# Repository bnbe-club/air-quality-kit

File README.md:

# air-quality-kit
The design files for the air quality kit based on the Piksey Pico and SGP30 sensor.

YouTube Video: https://www.youtube.com/watch?v=lpBCYy5J5to
Website Post: https://www.bitsnblobs.com/air-quality-sensor-kit

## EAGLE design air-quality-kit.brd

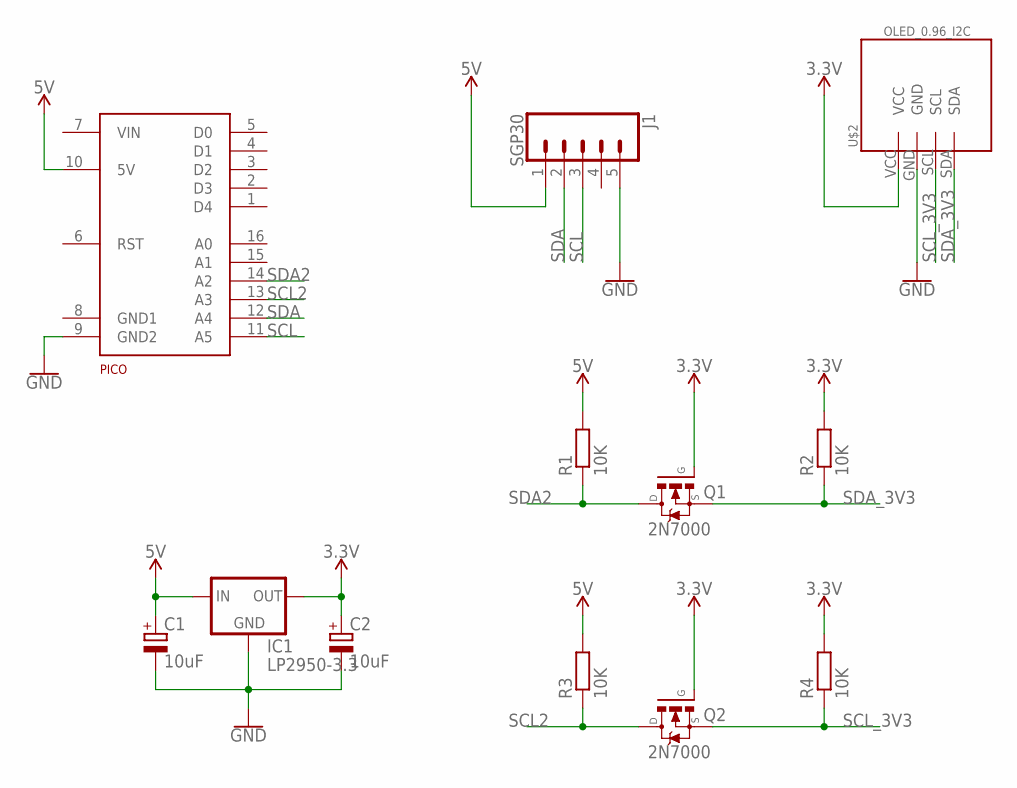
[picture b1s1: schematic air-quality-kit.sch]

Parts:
C1, C2: 10uF; E2,5-5
IC1: LP2950-3.3; TO92
J1: SGP30; 1X05
PICO: PICO
Q1, Q2: 2N7000; TO-92
R1, R2, R3, R4: 10K; 0207/10
U$2: OLED_0.96_I2C

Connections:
3.3V: C2.+, IC1.1 (OUT), Q1.2 (G), Q2.2 (G), R2.2, R4.2, U$2.VCC
5V: C1.+, IC1.3 (IN), J1.1, PICO.10 (5V), R1.2, R3.2
GND: C1.-, C2.-, IC1.2 (GND), J1.5, PICO.9 (GND2), U$2.GND
SCL: J1.3, PICO.11 (A5)
SCL2: PICO.13 (A3), Q2.3 (D), R3.1
SCL_3V3: Q2.1 (S), R4.1, U$2.SCL
SDA: J1.2, PICO.12 (A4)
SDA2: PICO.14 (A2), Q1.3 (D), R1.1
SDA_3V3: Q1.1 (S), R2.1, U$2.SDA

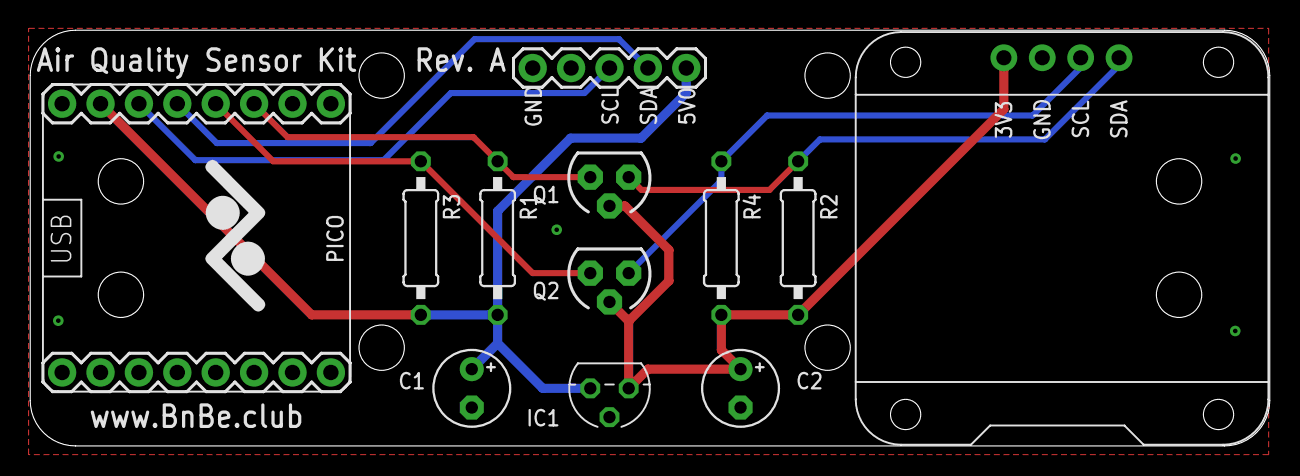
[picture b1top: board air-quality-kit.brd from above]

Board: 2 copper layers, 82.0 x 27.5 mm, 12 parts (0 on the bottom side), 9 nets.

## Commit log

2019-12-14 Added files for rev. A
2019-12-14 Added YouTube and website links

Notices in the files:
parts and their libraries:
SparkFun-Connectors: Licensing: Creative Commons ShareAlike 4.0 International - https://creativecommons.org/licenses/by-sa/4.0
